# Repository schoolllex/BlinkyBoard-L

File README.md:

**BlinkyBoard-L**
PCB Card follow the tutorial and little decoration for not expensive components

## Overview
Features:
- Beautiful
- Personnalized
- Works
- Not expensive

## Hardware
BOM at the end of file and in REPO
[Gerber](/555led/)
[Kicad schm](/555led/)
[Kicad pcb](/555led/)

## Inspo

This project was inspired by a Hack Club tutorial about making a PCB using a 555 timer and a decade counter.

I thought it would be a fun little project to follow the tutorial, while adding my own PCB design and a small personalized decoration.

The goal was to keep the project simple, cheap and fun, while still creating a real PCB that I could manufacture and assemble myself.

The original tutorial did not provide a complete BOM, so I had to find and select the components myself, mainly using AliExpress.

## BOM

Here is the BOM:
| # | Composant | Prix (€) | Prix ($) | Lien |
| --- | --- | --- | --- | --- |
| 1 | PCB | 3,00 € | $3,48 | - |
| 2 | Rubycon 50YXF1MEFC5X11 | 0,54 € | $0,63 | [Lien](https://www.lcsc.com/product-detail/C2927584.html) |
| 3 | CL05B103KB5NNNC | 0,59 € | $0,68 | [Lien](https://www.lcsc.com/product-detail/C15195.html) |
| 4 | TJ-L3FYTGHKMCGSFLC7K-A5 | 0,59 € | $0,68 | [Lien](https://www.lcsc.com/product-detail/C330747.html) |
| 5 | C5305 | 0,50 € | $0,58 | [Lien](https://www.lcsc.com/product-detail/C5305.html) |
| 6 | C52016392 | 0,65 € | $0,75 | [Lien](https://www.lcsc.com/product-detail/C52016392.html) |
| 7 | ST-4ETG 1K OHM (102) | 0,79 € | $0,92 | [Lien](https://www.lcsc.com/product-detail/C132881.html) |
| 8 | MFR-25FTE52-470R | 0,90 € | $1,04 | [Lien](https://www.lcsc.com/product-detail/C173020.html) |
| 9 | T93YA503KT20 | 3,43 € | $3,98 | [Lien](https://www.lcsc.com/product-detail/C7061697.html) |
| 10 | NE555P | 1,35 € | $1,57 | [Lien](https://www.lcsc.com/product-detail/C46749.html) |
| 11 | CD4017BED | 0,60 € | $0,70 | [Lien](https://www.lcsc.com/product-detail/C51898328.html) |
|  | **Total des composants listés** | **12,94 €** | **$15,01** |  |
|  | **Total annoncé** | **12,94 €** | **$15,01** |  |

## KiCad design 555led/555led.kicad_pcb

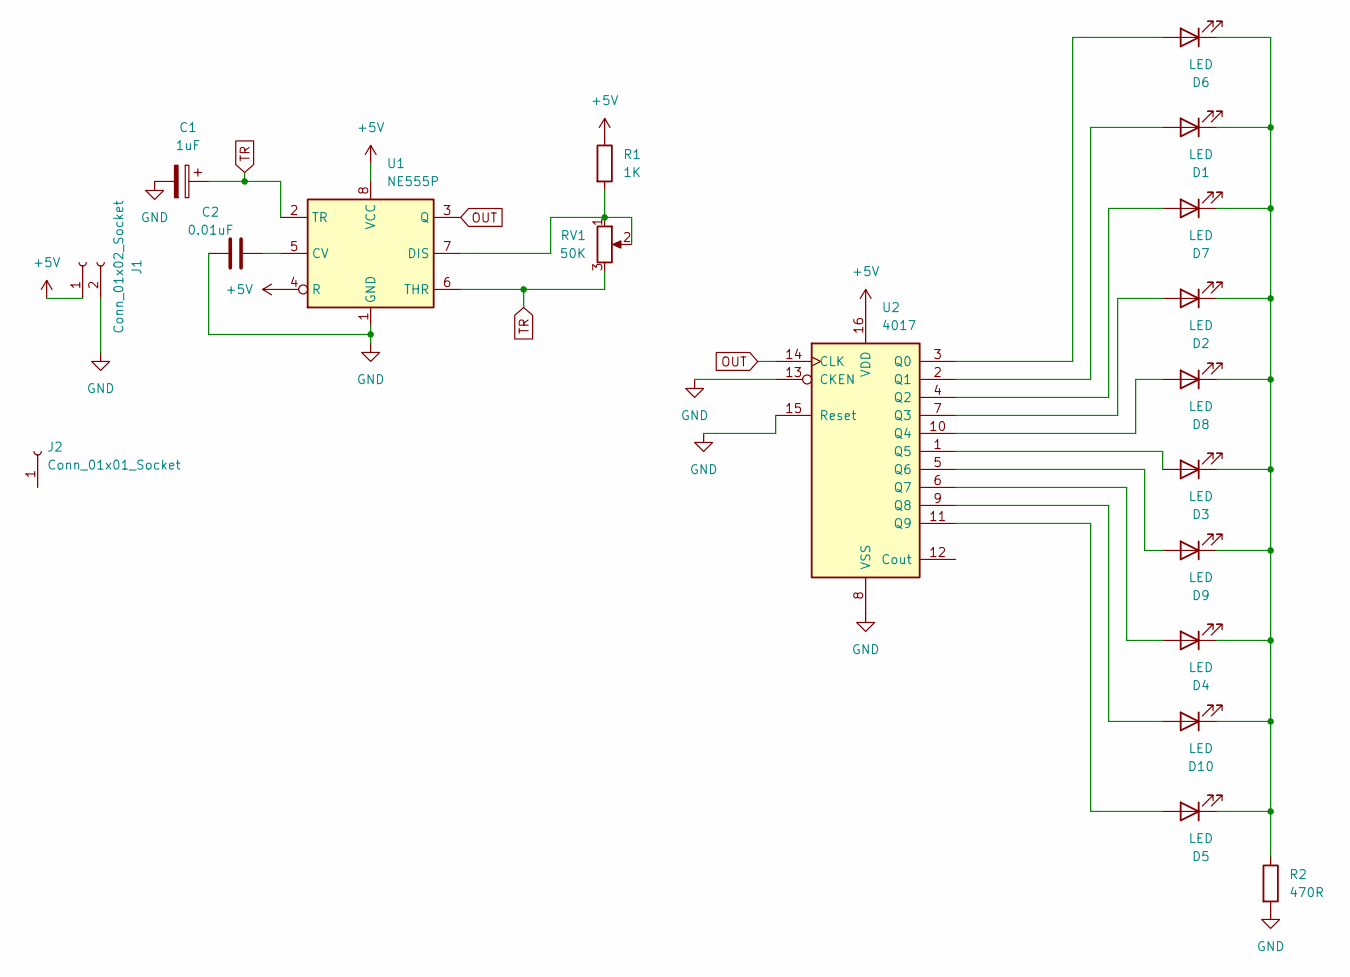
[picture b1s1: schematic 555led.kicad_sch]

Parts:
C1: 1uF; CP_Radial_D5.0mm_P2.00mm
C2: 0.01uF; C_Disc_D7.5mm_W2.5mm_P5.00mm
D1, D2, D3, D4, D5, D6, D7, D8, D9, D10: LED; LED_D3.0mm
J1: Conn_01x02_Socket; PinHeader_1x02_P2.54mm_Vertical
J2: Conn_01x01_Socket; PinHeader_1x01_P2.54mm_Vertical
R1: 1K; R_Axial_DIN0207_L6.3mm_D2.5mm_P7.62mm_Horizontal
R2: 470R; R_Axial_DIN0207_L6.3mm_D2.5mm_P7.62mm_Horizontal
RV1: 50K; Potentiometer_Vishay_T93YA_Vertical
U1: NE555P; DIP-8_W7.62mm
U2: 4017; N16

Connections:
+5V: J1.1, R1.1, U1.4 (R), U1.8 (VCC), U2.16 (VDD)
GND: C1.2, C2.1, J1.2, R2.2, U1.1 (GND), U2.8 (VSS), U2.13 (CKEN), U2.15 (Reset)
unnamed: D1.2 (A), U2.2 (Q1)
unnamed: D1.1 (K), D2.1 (K), D3.1 (K), D4.1 (K), D5.1 (K), D6.1 (K), D7.1 (K), D8.1 (K), D9.1 (K), D10.1 (K), R2.1
unnamed: D2.2 (A), U2.7 (Q3)
unnamed: D3.2 (A), U2.1 (Q5)
unnamed: D4.2 (A), U2.6 (Q7)
unnamed: D5.2 (A), U2.11 (Q9)
unnamed: D6.2 (A), U2.3 (Q0)
unnamed: D7.2 (A), U2.4 (Q2)
unnamed: D8.2 (A), U2.10 (Q4)
unnamed: D9.2 (A), U2.5 (Q6)
unnamed: D10.2 (A), U2.9 (Q8)
unnamed: C2.2, U1.5 (CV)
unnamed: R1.2, RV1.1, RV1.2, U1.7 (DIS)
OUT: U1.3 (Q), U2.14 (CLK)
TR: C1.1, RV1.3, U1.2 (TR), U1.6 (THR)

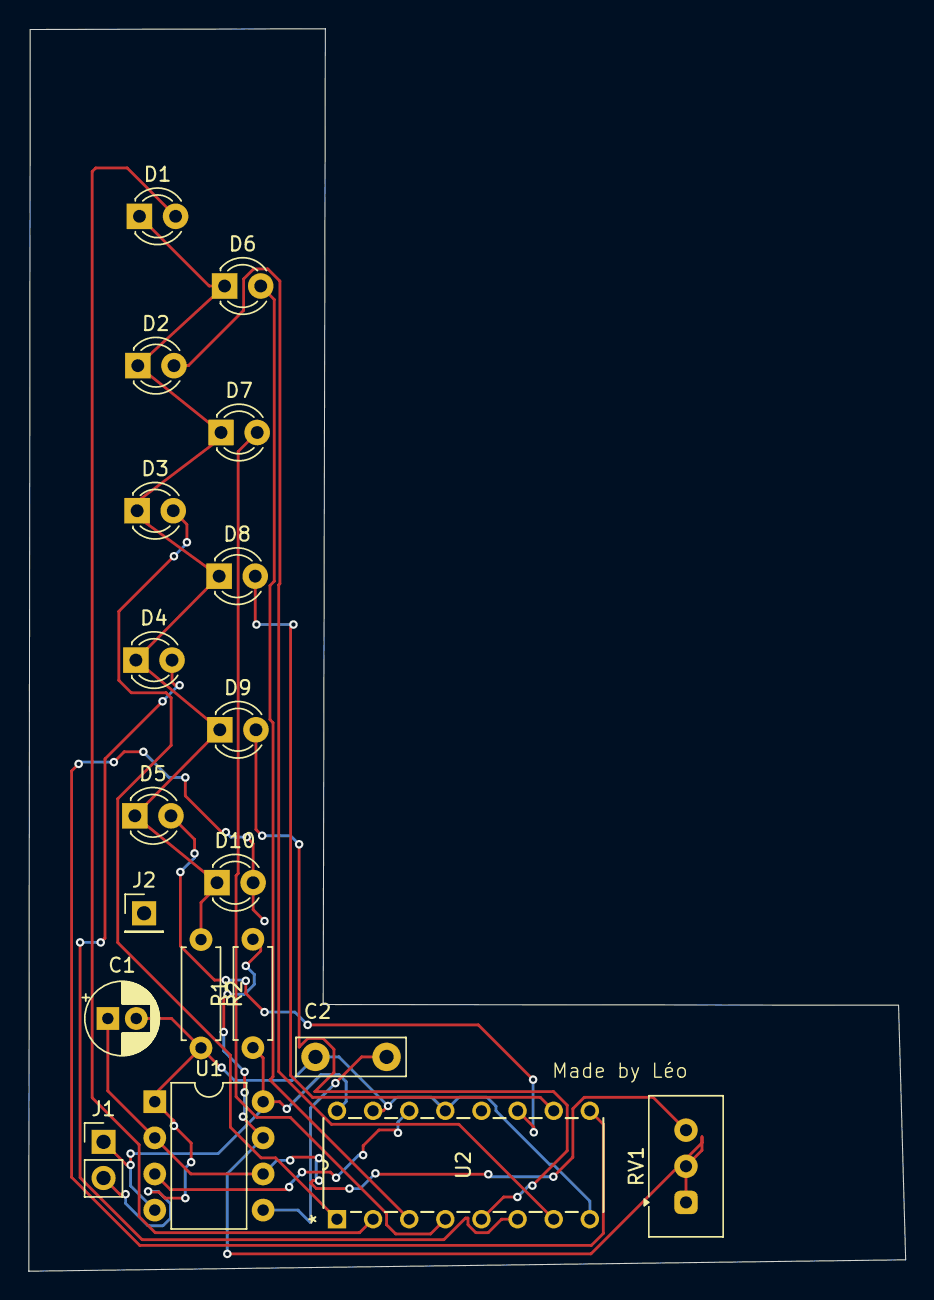
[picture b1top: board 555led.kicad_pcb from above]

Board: 2 copper layers, 61.6 x 87.3 mm, 19 parts (0 on the bottom side), 17 nets.

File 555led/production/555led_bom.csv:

Designator,Footprint,Quantity,Value,LCSC Part #
C1,CP_Radial_D5.0mm_P2.00mm,1,1uF,
C2,C_Disc_D7.5mm_W2.5mm_P5.00mm,1,0.01uF,
"D1, D10, D2, D3, D4, D5, D6, D7, D8, D9",LED_D3.0mm,10,LED,
J1,PinHeader_1x02_P2.54mm_Vertical,1,Conn_01x02_Socket,
J2,PinHeader_1x01_P2.54mm_Vertical,1,Conn_01x01_Socket,
R1,R_Axial_DIN0207_L6.3mm_D2.5mm_P7.62mm_Horizontal,1,1K,
R2,R_Axial_DIN0207_L6.3mm_D2.5mm_P7.62mm_Horizontal,1,470R,
RV1,Potentiometer_Vishay_T93YA_Vertical,1,50K,
U1,DIP-8_W7.62mm,1,NE555P,
U2,N16,1,4017,
